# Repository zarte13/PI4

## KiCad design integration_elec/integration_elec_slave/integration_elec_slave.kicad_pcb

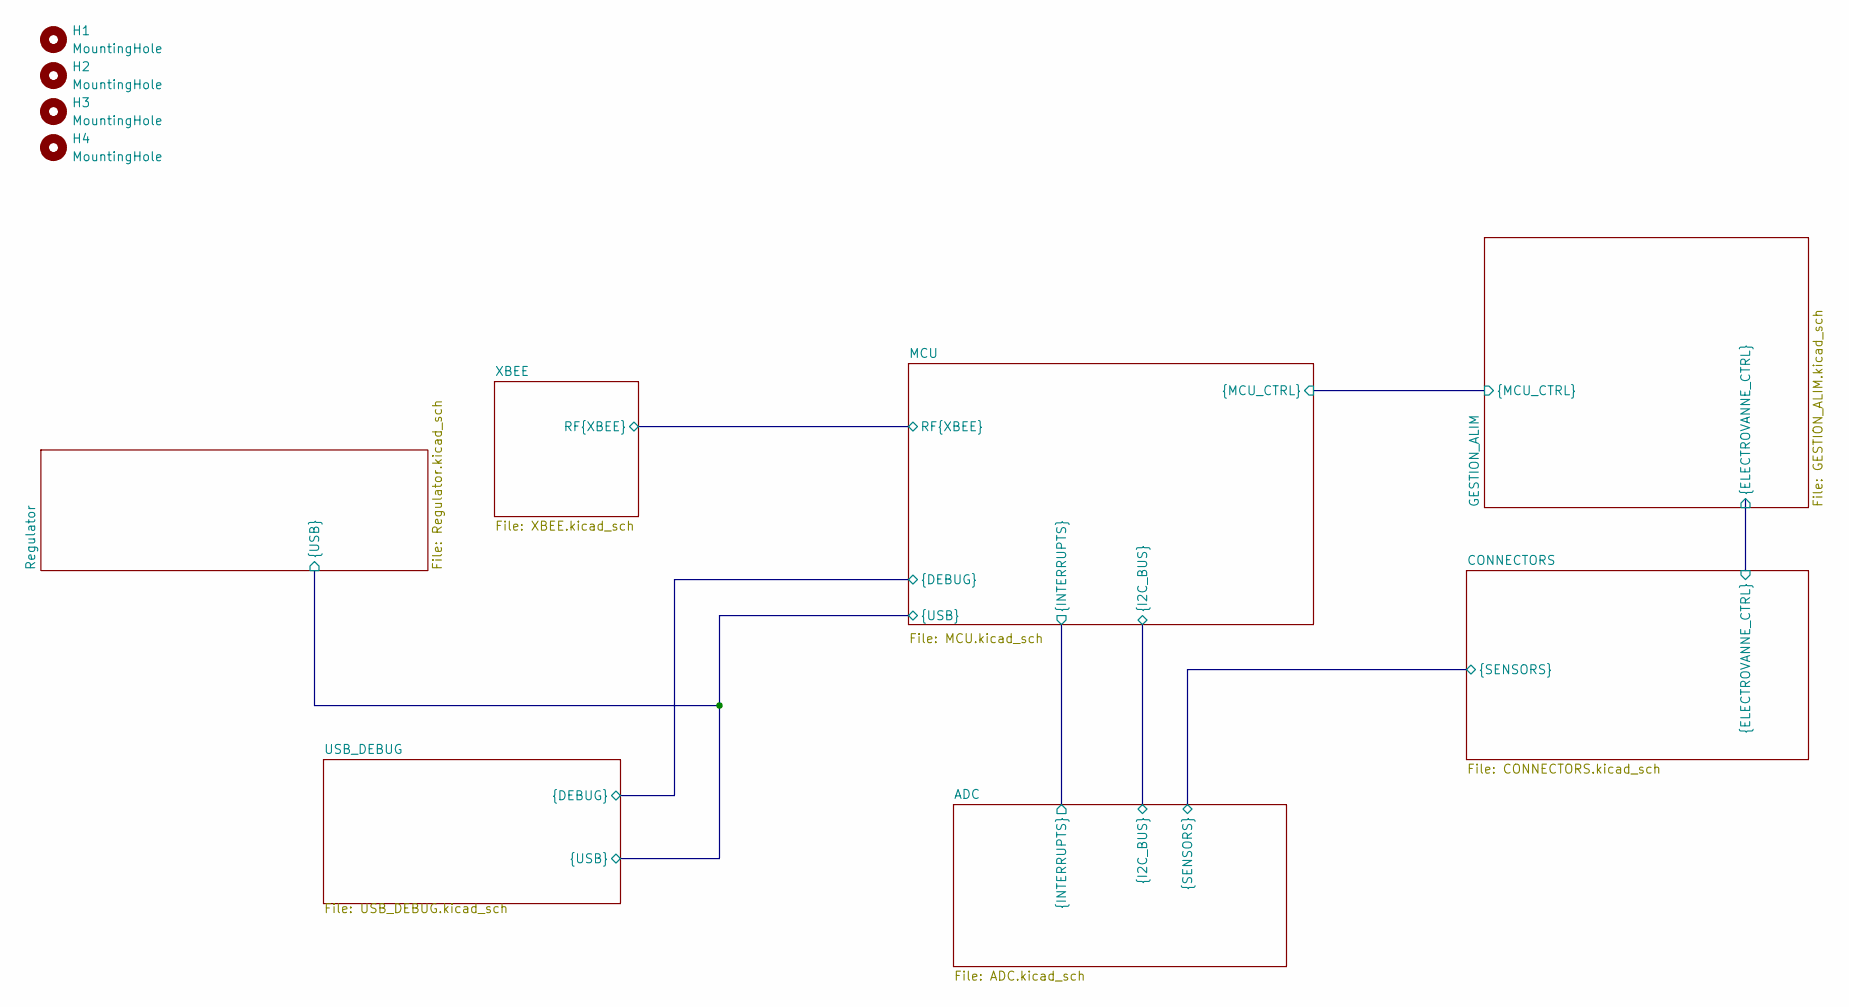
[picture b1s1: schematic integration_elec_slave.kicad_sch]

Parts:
H1, H2, H3, H4: MountingHole; MountingHole_3.2mm_M3

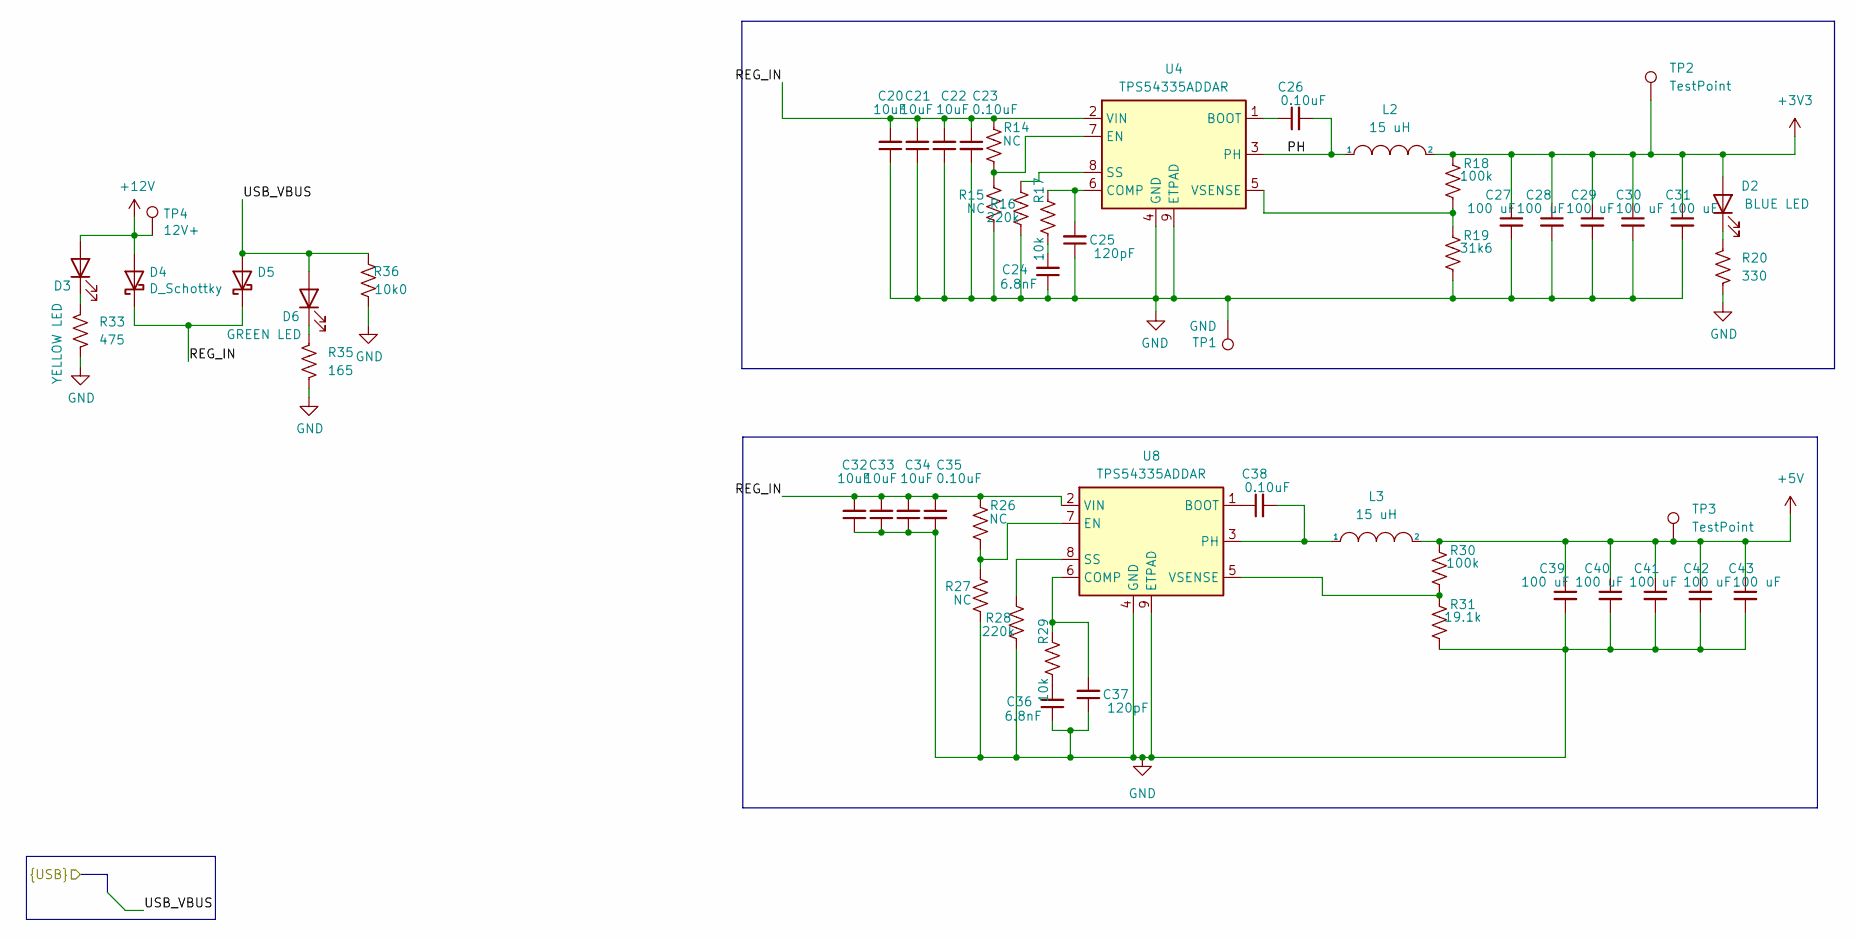
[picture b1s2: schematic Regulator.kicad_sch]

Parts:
C20, C21, C22, C32, C33, C34: 10uF; C_0805_2012Metric_Pad1.18x1.45mm_HandSolder; Manufacturer Part Number CL21A106KOQNNNE; DigiKey 1276-1096-1-ND
C23, C26, C35, C38: 0.10uF; C_0805_2012Metric_Pad1.18x1.45mm_HandSolder; Manufacturer Part Number CL21B104KBCNNNC; DigiKey 1276-1003-2-ND
C24, C36: 6.8nF; C_0805_2012Metric_Pad1.18x1.45mm_HandSolder; Manufacturer Part Number C0805C682K5RAC7800; DigiKey 399-C0805C682K5RAC7800TR-ND
C25, C37: 120pF; C_0805_2012Metric_Pad1.18x1.45mm_HandSolder; Manufacturer Part Number C0805C121J5GAC7800; DigiKey 399-C0805C121J5GAC7800TR-ND
C27, C28, C29, C30, C31, C39, C40, C41, C42, C43: 100 uF; C_1206_3216Metric; Manufacturer Part Number GRM31CR61A107MEA8L; DigiKey 490-GRM31CR61A107MEA8LTR-ND
D2: BLUE LED; LED_0805_2012Metric_Pad1.15x1.40mm_HandSolder; Manufacturer Part Number 5973605607F; DigiKey 350-4394-1-ND
D3: YELLOW LED; LED_1206_3216Metric; Manufacturer Part Number QTLP650D3TR; DigiKey 1080-1418-2-ND
D4, D5: D_Schottky; SOD323-HE; Manufacturer Part Number MBR1060HEWS_R1_00001; DigiKey 3757-MBR1060HEWS_R1_00001CT-ND
D6: GREEN LED; LED_1206_3216Metric; Manufacturer Part Number 5973605607F; DigiKey 350-4394-1-ND
L2, L3: 15 uH; IND_BOURNS_SRR1280; Manufacturer Part Number SRR1280-150M; DigiKey SRR1280-150MTR-ND
R14, R15, R26, R27: NC; R_0805_2012Metric_Pad1.20x1.40mm_HandSolder
R16, R28: 220k; R_0805_2012Metric_Pad1.20x1.40mm_HandSolder; Manufacturer Part Number CRG0805F220K; DigiKey A126350CT-ND
R17, R29: 10k; R_0805_2012Metric_Pad1.20x1.40mm_HandSolder; Manufacturer Part Number RC0805FR-0710KL; DigiKey 311-10.0KCRCT-ND
R18, R30: 100k; R_0805_2012Metric_Pad1.20x1.40mm_HandSolder; Manufacturer Part Number RC0805FR-07100KL; DigiKey 311-100KCRTR-ND
R19: 31k6; R_0805_2012Metric_Pad1.20x1.40mm_HandSolder; Manufacturer Part Number RC0805FR-0731K6L; DigiKey 311-31.6KCRTR-ND
R20: 330; R_0805_2012Metric_Pad1.20x1.40mm_HandSolder; Manufacturer Part Number RC0805JR-07330RL; DigiKey 311-330ARCT-ND
R31: 19.1k; R_0805_2012Metric_Pad1.20x1.40mm_HandSolder; DigiKey 311-19.1KCRCT-ND
R33: 475; R_0805_2012Metric_Pad1.20x1.40mm_HandSolder; Manufacturer Part Number RNCP0805FTD475R; DigiKey RNCP0805FTD475RTR-ND
R35: 165; R_0805_2012Metric_Pad1.20x1.40mm_HandSolder; Manufacturer Part Number RC0805FR-07165RL; DigiKey 311-165CRTR-ND
R36: 10k0; R_0603_1608Metric_Pad0.98x0.95mm_HandSolder; Manufacturer Part Number RC0805FR-0710KL; DigiKey 311-10.0KHRCT-ND
TP1: GND; TestPoint_Plated_Hole_D2.0mm
TP2, TP3: TestPoint; TestPoint_Plated_Hole_D2.0mm
TP4: 12V+; TestPoint_Plated_Hole_D2.0mm
U4, U8: TPS54335ADDAR; TI_SO-PowerPAD-8_ThermalVias; Manufacturer Part Number TPS54335ADDAR; DigiKey 296-TPS54335ADDARTR-ND

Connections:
+3V3: C27.1, C28.1, C29.1, C30.1, C31.1, D2.2 (A), L2.2, R18.1, TP2.1; also elsewhere on the board
+5V: C39.1, C40.1, C41.1, C42.1, C43.1, L3.2, R30.1, TP3.1; also elsewhere on the board
+12V: D3.2 (A), D4.2 (A), TP4.1; also elsewhere on the board
/MCU/USB_VBUS: D5.2 (A), D6.2 (A), R36.1; also elsewhere on the board
/Regulator/PH: C26.2, L2.1, U4.3 (PH)
/Regulator/REG_IN: C20.2, C21.2, C22.2, C23.1, C32.2, C33.2, C34.2, C35.1, D4.1 (K), D5.1 (K), R14.1, R26.1, U4.2 (VIN), U8.2 (VIN)
GND: C20.1, C21.1, C22.1, C23.2, C24.1, C25.1, C27.2, C28.2, C29.2, C30.2, C31.2, C32.1, C33.1, C34.1, C35.2, C36.1, C37.1, C39.2, C40.2, C41.2, C42.2, C43.2, R15.2, R16.2, R19.2, R20.2, R27.2, R28.2, R31.2, R33.2, R35.2, R36.2, TP1.1, U4.4 (GND), U4.9 (ETPAD), U8.4 (GND), U8.9 (ETPAD); also elsewhere on the board
unnamed: C24.2, R17.2
unnamed: C36.2, R29.2
unnamed: D2.1 (K), R20.1
unnamed: D3.1 (K), R33.1
unnamed: D6.1 (K), R35.1
unnamed: C26.1, U4.1 (BOOT)
unnamed: C25.2, R17.1, U4.6 (COMP)
unnamed: R14.2, R15.1, U4.7 (EN)
unnamed: R16.1, U4.8 (SS)
unnamed: R18.2, R19.1, U4.5 (VSENSE)
unnamed: C38.1, U8.1 (BOOT)
unnamed: C37.2, R29.1, U8.6 (COMP)
unnamed: R26.2, R27.1, U8.7 (EN)
unnamed: C38.2, L3.1, U8.3 (PH)
unnamed: R28.1, U8.8 (SS)
unnamed: R30.2, R31.1, U8.5 (VSENSE)

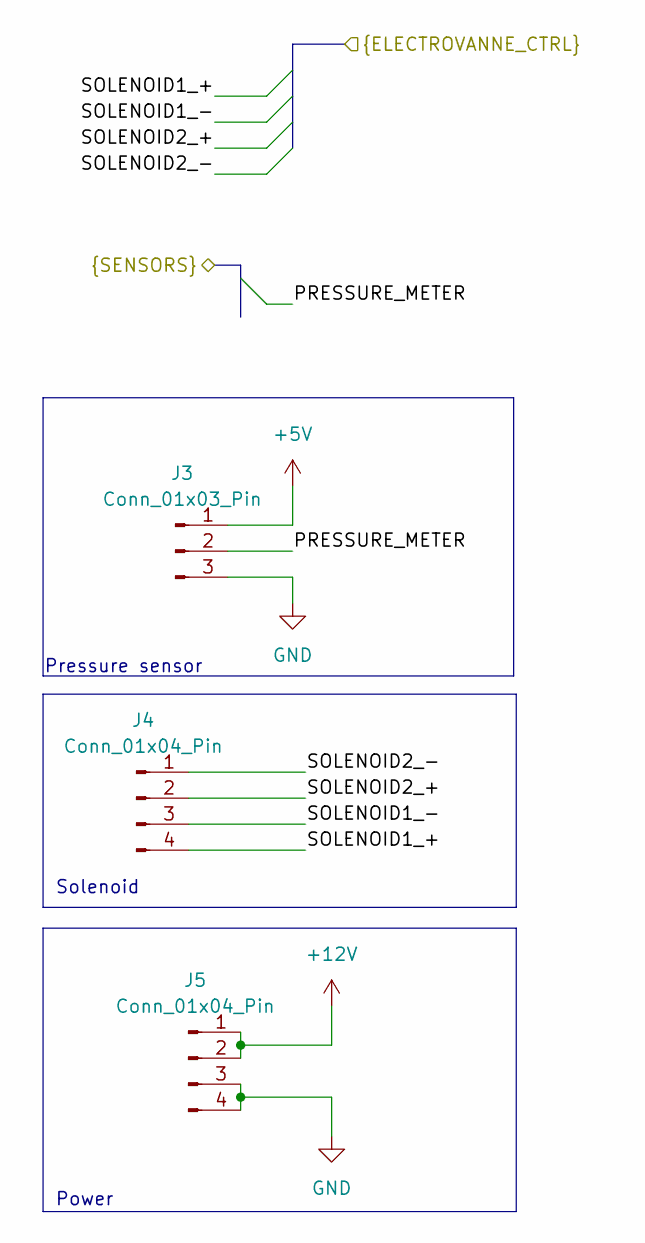
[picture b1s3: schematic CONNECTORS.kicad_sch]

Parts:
J3: Conn_01x03_Pin; Molex_Micro-Fit_3.0_43650-0315_1x03_P3.00mm_Vertical; DigiKey 538-43650-0315
J4, J5: Conn_01x04_Pin; Molex_Micro-Fit_3.0_43650-0415_1x04_P3.00mm_Vertical; DigiKey WM1919-ND

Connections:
+5V: J3.1; also elsewhere on the board
+12V: J5.1, J5.2; also elsewhere on the board
/ADC/PRESSURE_METER: J3.2; also elsewhere on the board
/CONNECTORS/SOLENOID1_+: J4.4; also elsewhere on the board
/CONNECTORS/SOLENOID1_-: J4.3; also elsewhere on the board
/CONNECTORS/SOLENOID2_+: J4.2; also elsewhere on the board
/CONNECTORS/SOLENOID2_-: J4.1; also elsewhere on the board
GND: J3.3, J5.3, J5.4; also elsewhere on the board

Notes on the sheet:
Pressure sensor
Power
Solenoid

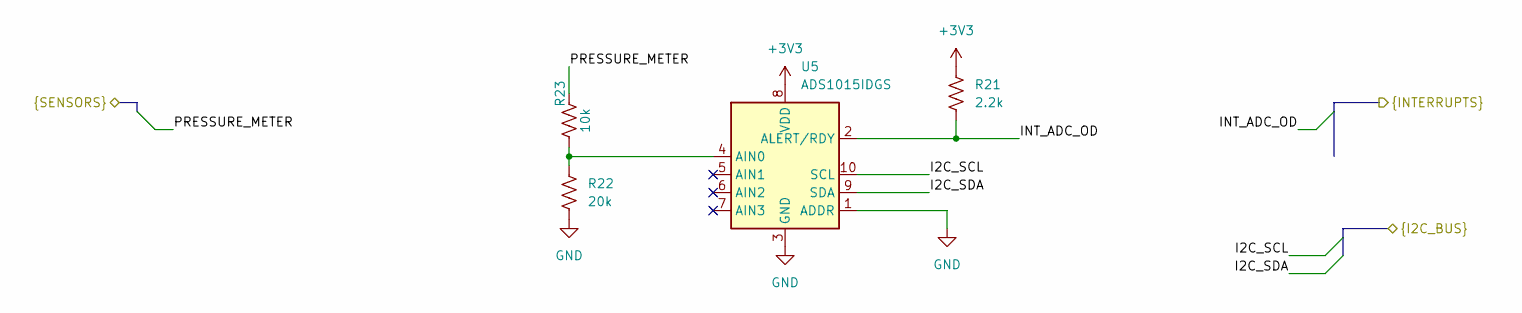
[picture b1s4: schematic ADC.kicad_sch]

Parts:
R21: 2.2k; R_0805_2012Metric_Pad1.20x1.40mm_HandSolder; DigiKey 311-2.20KCRCT-ND
R22: 20k; R_0805_2012Metric_Pad1.20x1.40mm_HandSolder; DigiKey P20KDACT-ND
R23: 10k; R_0805_2012Metric_Pad1.20x1.40mm_HandSolder; Manufacturer Part Number RC0805FR-0710KL; DigiKey 311-10.0KCRCT-ND
U5: ADS1015IDGS; TSSOP-10_3x3mm_P0.5mm; DigiKey 595-ADS1015IDGSR

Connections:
+3V3: R21.1, U5.8 (VDD); also elsewhere on the board
/ADC/I2C_SCL: U5.10 (SCL); also elsewhere on the board
/ADC/I2C_SDA: U5.9 (SDA); also elsewhere on the board
/ADC/INT_ADC_OD: R21.2, U5.2 (ALERT/RDY); also elsewhere on the board
/ADC/PRESSURE_METER: R23.1; also elsewhere on the board
GND: R22.2, U5.1 (ADDR), U5.3 (GND); also elsewhere on the board
unnamed: R22.1, R23.2, U5.4 (AIN0)

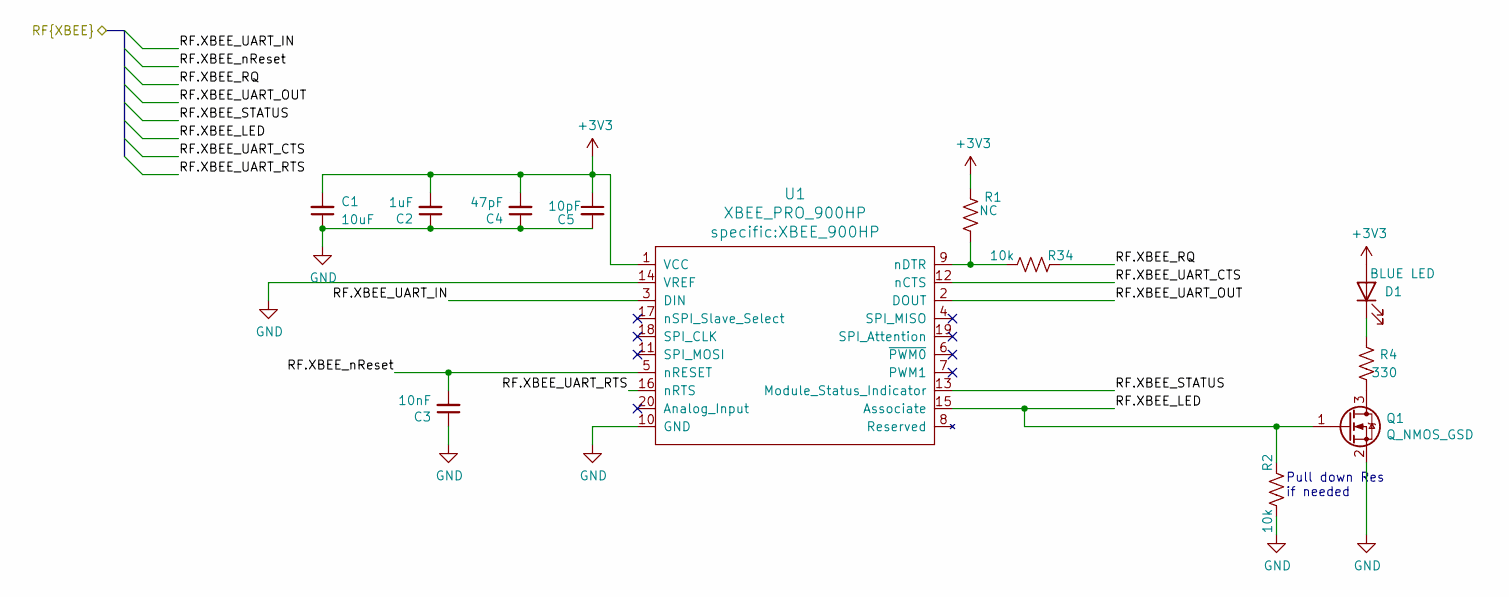
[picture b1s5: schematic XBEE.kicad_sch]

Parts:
C1: 10uF; C_0805_2012Metric_Pad1.18x1.45mm_HandSolder; Manufacturer Part Number CL21A106KOQNNNE; DigiKey 1276-1096-1-ND
C2: 1uF; C_0805_2012Metric_Pad1.18x1.45mm_HandSolder; Manufacturer Part Number C0805C105K4RAC7800; DigiKey 399-C0805C105K4RAC7800TR-ND
C3: 10nF; C_0805_2012Metric_Pad1.18x1.45mm_HandSolder; Manufacturer Part Number CL21B103KBANNNC; DigiKey 1276-1015-1-ND
C4: 47pF; C_0805_2012Metric_Pad1.18x1.45mm_HandSolder; Manufacturer Part Number C0805C470J5GAC7210; DigiKey 399-C0805C470J5GAC7210TR-ND
C5: 10pF; C_0805_2012Metric_Pad1.18x1.45mm_HandSolder; Manufacturer Part Number C0805C100J5GAC7800; DigiKey 399-C0805C100J5GAC7800TR-ND
D1: BLUE LED; LED_0805_2012Metric_Pad1.15x1.40mm_HandSolder; Manufacturer Part Number 5973605607F; DigiKey 350-4394-1-ND
Q1: Q_NMOS_GSD; SOT-23; Manufacturer Part Number 2N7002-TP; DigiKey 2N7002-TPMSCT-ND
R1: NC; R_0805_2012Metric_Pad1.20x1.40mm_HandSolder
R2, R34: 10k; R_0805_2012Metric_Pad1.20x1.40mm_HandSolder; Manufacturer Part Number RC0805FR-0710KL; DigiKey 311-10.0KCRCT-ND
R4: 330; R_0805_2012Metric_Pad1.20x1.40mm_HandSolder; Manufacturer Part Number RC0805JR-07330RL; DigiKey 311-330ARCT-ND
U1: XBEE_PRO_900HP; XBEE_900HP; Manufacturer Part Number XBP9B-DMST-002; DigiKey 602-1299-ND

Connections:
+3V3: C1.2, C2.2, C4.2, C5.1, D1.2 (A), R1.1, U1.1 (VCC); also elsewhere on the board
/MCU/RF.XBEE_LED: Q1.1 (G), R2.1, U1.15 (Associate); also elsewhere on the board
/MCU/RF.XBEE_RQ: R34.1; also elsewhere on the board
/MCU/RF.XBEE_STATUS: U1.13 (Module_Status_Indicator); also elsewhere on the board
/MCU/RF.XBEE_UART_CTS: U1.12 (nCTS); also elsewhere on the board
/MCU/RF.XBEE_UART_IN: U1.3 (DIN); also elsewhere on the board
/MCU/RF.XBEE_UART_OUT: U1.2 (DOUT); also elsewhere on the board
/MCU/RF.XBEE_UART_RTS: U1.16 (nRTS); also elsewhere on the board
/MCU/RF.XBEE_nReset: C3.2, U1.5 (nRESET); also elsewhere on the board
GND: C1.1, C2.1, C3.1, C4.1, C5.2, Q1.2 (S), R2.2, U1.10 (GND), U1.14 (VREF); also elsewhere on the board
unnamed: D1.1 (K), R4.1
unnamed: Q1.3 (D), R4.2
unnamed: R1.2, R34.2, U1.9 (nDTR)

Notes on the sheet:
Pull down Res if needed

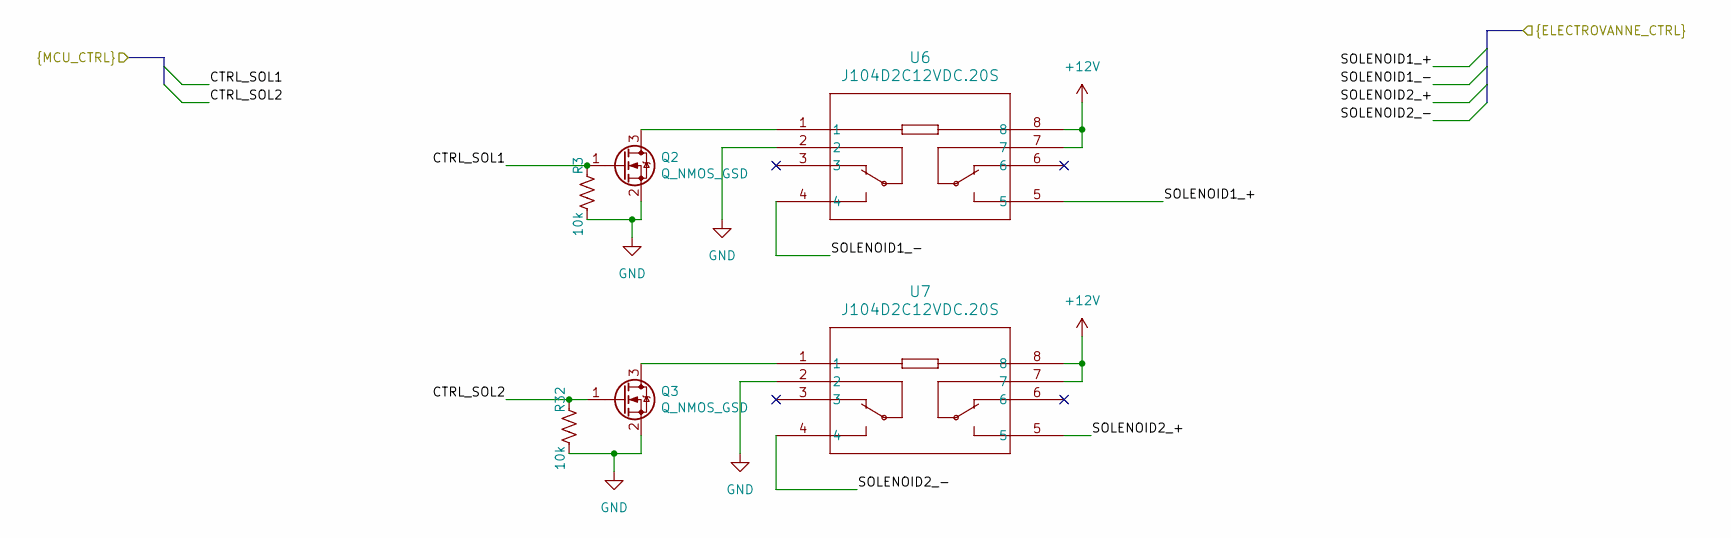
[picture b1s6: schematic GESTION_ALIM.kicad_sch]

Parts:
Q2, Q3: Q_NMOS_GSD; SOT-23; Manufacturer Part Number SQ2308CES-T1_GE3; DigiKey SQ2308CES-T1_GE3CT-ND
R3, R32: 10k; R_0805_2012Metric_Pad1.20x1.40mm_HandSolder; Manufacturer Part Number RC0805FR-0710KL; DigiKey 311-10.0KCRCT-ND
U6, U7: J104D2C12VDC.20S; RELAY8_J104D2C12VDC.20S_CRS; DigiKey 2449-J104D2C12VDC.20S-ND

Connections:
+12V: U6.7, U6.8, U7.7, U7.8; also elsewhere on the board
/CONNECTORS/SOLENOID1_+: U6.5; also elsewhere on the board
/CONNECTORS/SOLENOID1_-: U6.4; also elsewhere on the board
/CONNECTORS/SOLENOID2_+: U7.5; also elsewhere on the board
/CONNECTORS/SOLENOID2_-: U7.4; also elsewhere on the board
/GESTION_ALIM/CTRL_SOL1: Q2.1 (G), R3.1; also elsewhere on the board
/GESTION_ALIM/CTRL_SOL2: Q3.1 (G), R32.1; also elsewhere on the board
GND: Q2.2 (S), Q3.2 (S), R3.2, R32.2, U6.2, U7.2; also elsewhere on the board
unnamed: Q2.3 (D), U6.1
unnamed: Q3.3 (D), U7.1

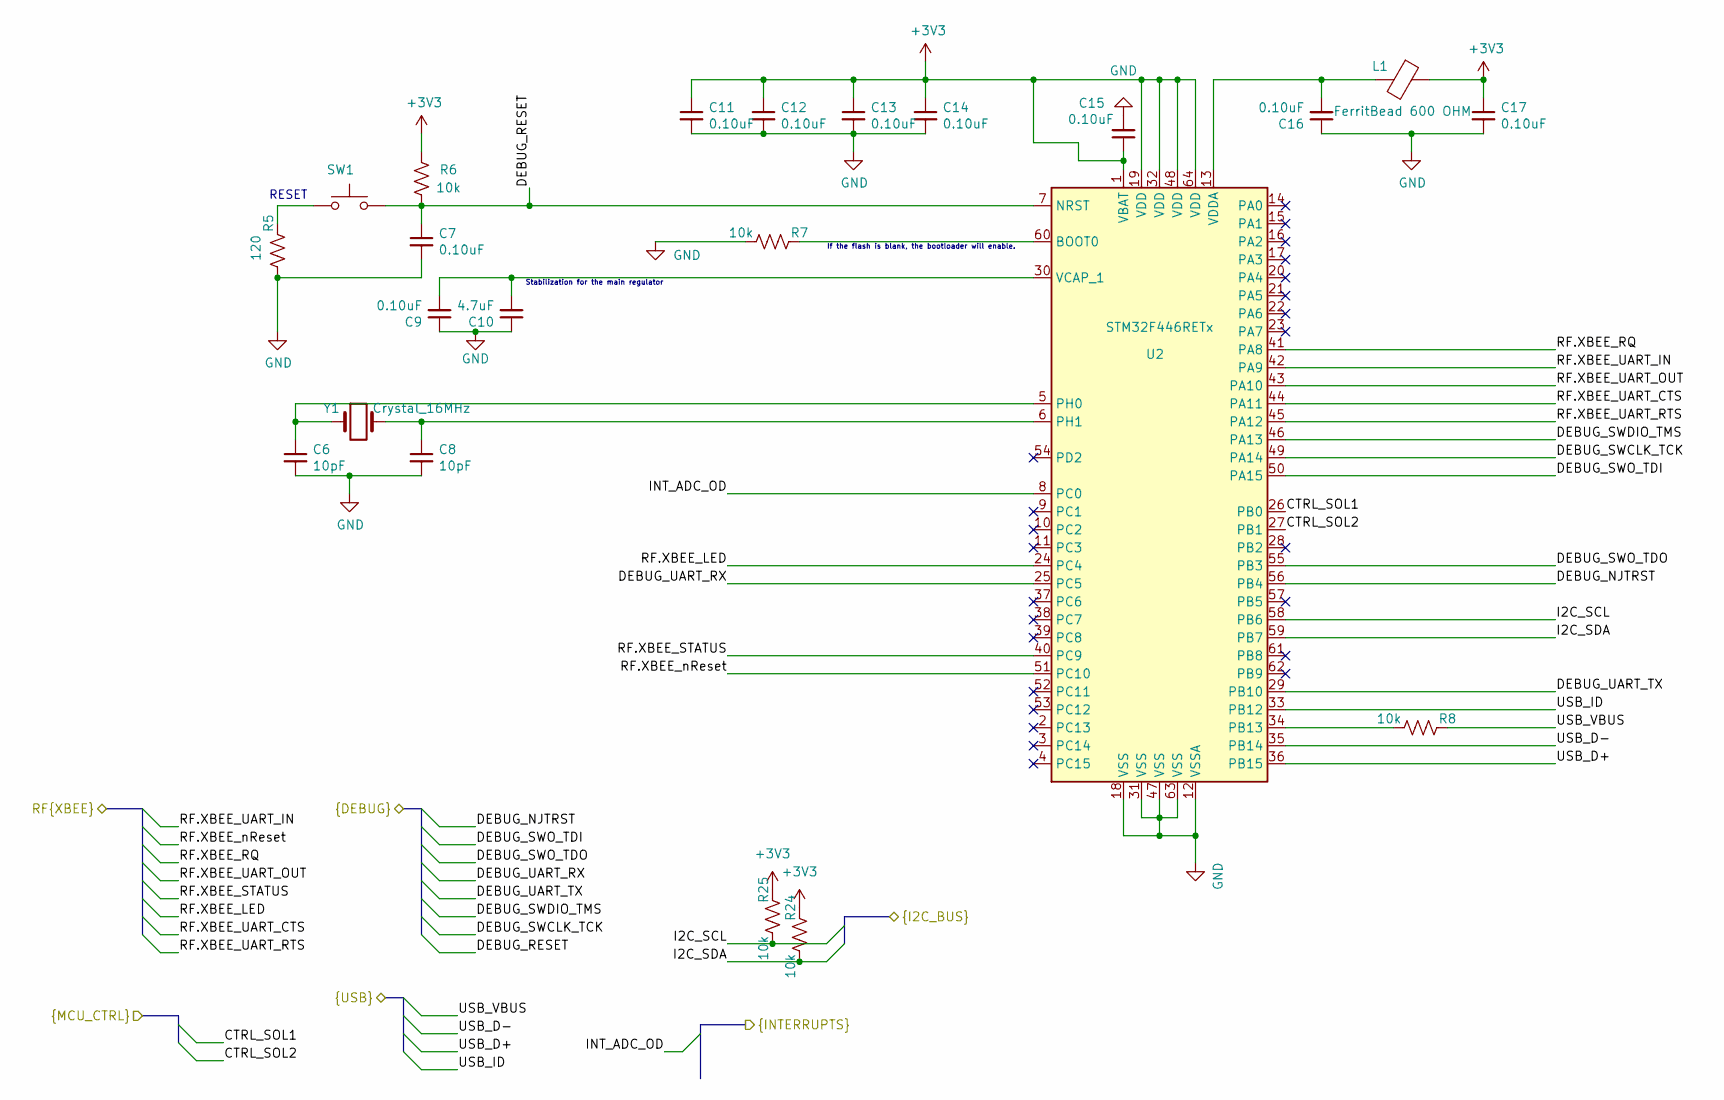
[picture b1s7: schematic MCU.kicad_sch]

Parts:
C6, C8: 10pF; C_0805_2012Metric_Pad1.18x1.45mm_HandSolder; Manufacturer Part Number C0805C100J5GAC7800; DigiKey 399-C0805C100J5GAC7800TR-ND
C7, C9, C11, C12, C13, C14, C15, C16, C17: 0.10uF; C_0805_2012Metric_Pad1.18x1.45mm_HandSolder; Manufacturer Part Number CL21B104KBCNNNC; DigiKey 1276-1003-2-ND
C10: 4.7uF; C_0805_2012Metric_Pad1.18x1.45mm_HandSolder; Manufacturer Part Number CL21A475KOFNNNE; DigiKey 1276-1065-1-ND
L1: FerritBead 600 OHM; L_0805_2012Metric_Pad1.15x1.40mm_HandSolder; Manufacturer Part Number 742792040; DigiKey 732-1620-1-ND
R5: 120; R_0805_2012Metric_Pad1.20x1.40mm_HandSolder; Manufacturer Part Number RC0805JR-07120RL; DigiKey 311-120ARCT-ND
R6, R7, R8, R24, R25: 10k; R_0805_2012Metric_Pad1.20x1.40mm_HandSolder; Manufacturer Part Number RC0805FR-0710KL; DigiKey 311-10.0KCRCT-ND
SW1: SW_Push; SW_SPST_TL3342; Manufacturer Part Number TL3342F160QG/TR; DigiKey EG2531CT-ND
U2: STM32F446RETx; LQFP-64_10x10mm_P0.5mm; Manufacturer Part Number STM32F446RET6; DigiKey 497-15376-ND
Y1: Crystal_16MHz; CSM-3X; Manufacturer Part Number ECS-160-20-3X-TR; DigiKey XC1776CT-ND

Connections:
+3V3: C11.1, C12.1, C13.1, C14.1, C15.1, C17.1, L1.1, R6.1, R24.1, R25.1, U2.1 (VBAT), U2.19 (VDD), U2.32 (VDD), U2.48 (VDD), U2.64 (VDD); also elsewhere on the board
/ADC/I2C_SCL: R25.2, U2.58 (PB6); also elsewhere on the board
/ADC/I2C_SDA: R24.2, U2.59 (PB7); also elsewhere on the board
/ADC/INT_ADC_OD: U2.8 (PC0); also elsewhere on the board
/GESTION_ALIM/CTRL_SOL1: U2.26 (PB0); also elsewhere on the board
/GESTION_ALIM/CTRL_SOL2: U2.27 (PB1); also elsewhere on the board
/MCU/DEBUG_NJTRST: U2.56 (PB4); also elsewhere on the board
/MCU/DEBUG_RESET: C7.1, R6.2, SW1.2, U2.7 (NRST); also elsewhere on the board
/MCU/DEBUG_SWCLK_TCK: U2.49 (PA14); also elsewhere on the board
/MCU/DEBUG_SWDIO_TMS: U2.46 (PA13); also elsewhere on the board
/MCU/DEBUG_SWO_TDI: U2.50 (PA15); also elsewhere on the board
/MCU/DEBUG_SWO_TDO: U2.55 (PB3); also elsewhere on the board
/MCU/DEBUG_UART_RX: U2.25 (PC5); also elsewhere on the board
/MCU/DEBUG_UART_TX: U2.29 (PB10); also elsewhere on the board
/MCU/RF.XBEE_LED: U2.24 (PC4); also elsewhere on the board
/MCU/RF.XBEE_RQ: U2.41 (PA8); also elsewhere on the board
/MCU/RF.XBEE_STATUS: U2.40 (PC9); also elsewhere on the board
/MCU/RF.XBEE_UART_CTS: U2.44 (PA11); also elsewhere on the board
/MCU/RF.XBEE_UART_IN: U2.42 (PA9); also elsewhere on the board
/MCU/RF.XBEE_UART_OUT: U2.43 (PA10); also elsewhere on the board
/MCU/RF.XBEE_UART_RTS: U2.45 (PA12); also elsewhere on the board
/MCU/RF.XBEE_nReset: U2.51 (PC10); also elsewhere on the board
/MCU/USB_D+: U2.36 (PB15); also elsewhere on the board
/MCU/USB_D-: U2.35 (PB14); also elsewhere on the board
/MCU/USB_ID: U2.33 (PB12)
/MCU/USB_VBUS: R8.1; also elsewhere on the board
GND: C6.2, C7.2, C8.2, C9.1, C10.1, C11.2, C12.2, C13.2, C14.2, C15.2, C16.1, C17.2, R5.2, R7.2, U2.12 (VSSA), U2.18 (VSS), U2.31 (VSS), U2.47 (VSS), U2.63 (VSS); also elsewhere on the board
unnamed: R5.1, SW1.1
unnamed: R7.1, U2.60 (BOOT0)
unnamed: R8.2, U2.34 (PB13)
unnamed: C6.1, U2.5 (PH0), Y1.1
unnamed: C8.1, U2.6 (PH1), Y1.2
unnamed: C9.2, C10.2, U2.30 (VCAP_1)
unnamed: C16.2, L1.2, U2.13 (VDDA)

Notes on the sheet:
RESET
If the flash is blank, the bootloader will enable.
Stabilization for the main regulator

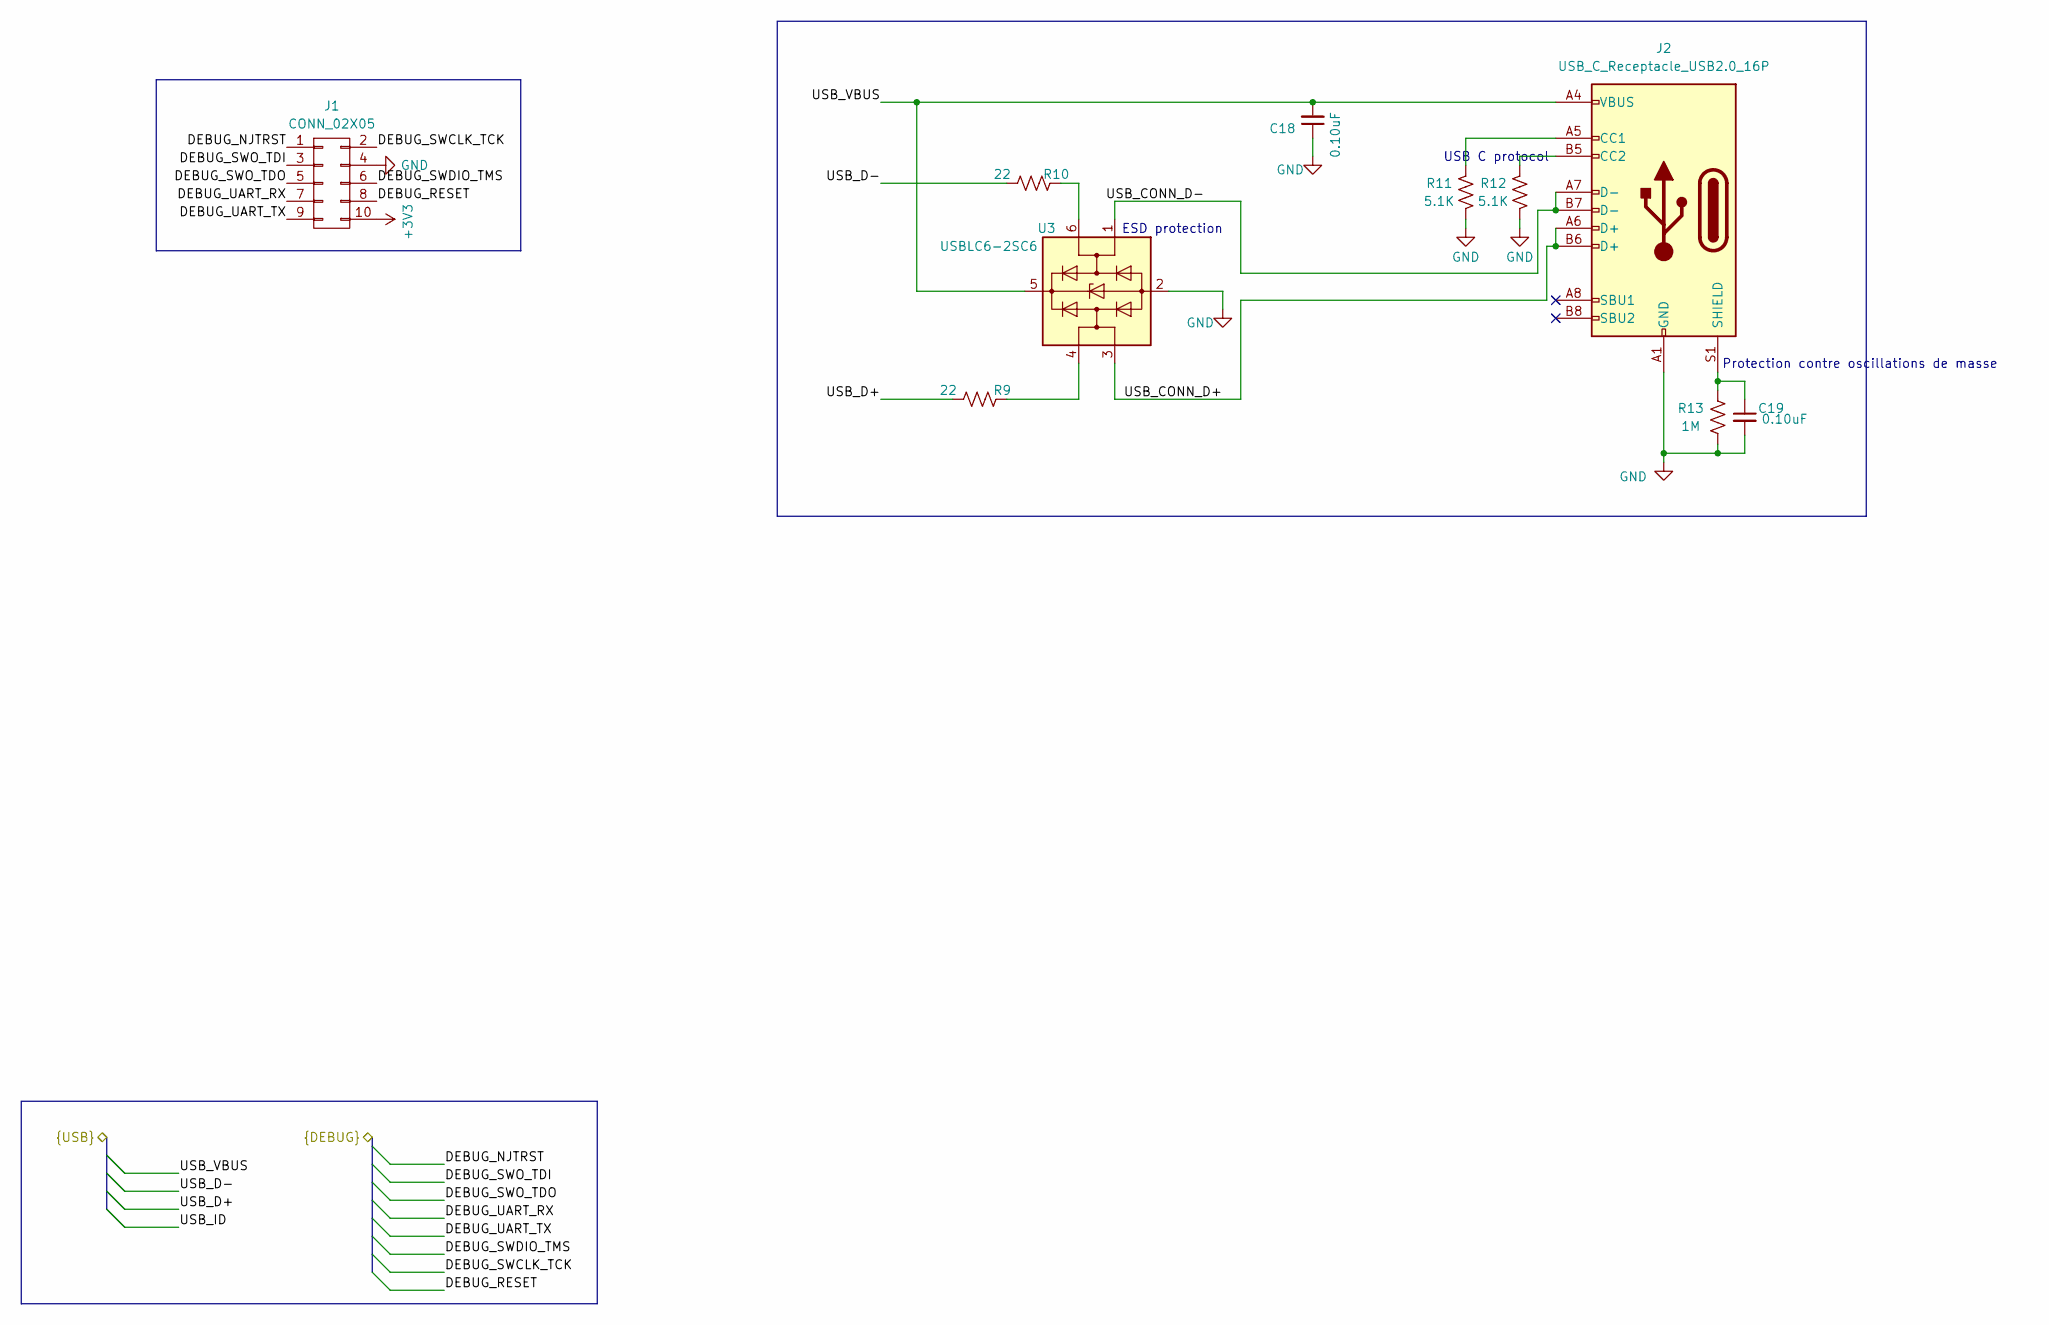
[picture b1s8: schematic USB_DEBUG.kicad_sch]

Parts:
C18, C19: 0.10uF; C_0805_2012Metric_Pad1.18x1.45mm_HandSolder; Manufacturer Part Number CL21B104KBCNNNC; DigiKey 1276-1003-2-ND
J1: CONN_02X05; CONN_CNC_10_pins; DigiKey 1175-1627-ND
J2: USB_C_Receptacle_USB2.0_16P; USB_C_Receptacle_GCT_USB4105-xx-A_16P_TopMnt_Horizontal; DigiKey 2073-USB4105-GF-ACT-ND
R9, R10: 22; R_0805_2012Metric_Pad1.20x1.40mm_HandSolder; Manufacturer Part Number RC0805JR-0722RL; DigiKey 311-22ARCT-ND
R11, R12: 5.1K; R_0603_1608Metric_Pad0.98x0.95mm_HandSolder; DigiKey 311-5.10KHRCT-ND
R13: 1M; R_0805_2012Metric_Pad1.20x1.40mm_HandSolder; Manufacturer Part Number RC0805FR-071ML; DigiKey 311-1.00MCRTR-ND
U3: USBLC6-2SC6; SOT-23-6; Manufacturer Part Number USBLC6-2SC6Y; DigiKey 497-11882-1-ND

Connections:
+3V3: J1.10; also elsewhere on the board
/MCU/DEBUG_NJTRST: J1.1; also elsewhere on the board
/MCU/DEBUG_RESET: J1.8; also elsewhere on the board
/MCU/DEBUG_SWCLK_TCK: J1.2; also elsewhere on the board
/MCU/DEBUG_SWDIO_TMS: J1.6; also elsewhere on the board
/MCU/DEBUG_SWO_TDI: J1.3; also elsewhere on the board
/MCU/DEBUG_SWO_TDO: J1.5; also elsewhere on the board
/MCU/DEBUG_UART_RX: J1.7; also elsewhere on the board
/MCU/DEBUG_UART_TX: J1.9; also elsewhere on the board
/MCU/USB_D+: R9.2; also elsewhere on the board
/MCU/USB_D-: R10.2; also elsewhere on the board
/MCU/USB_VBUS: C18.2, J2.A4 (VBUS), J2.A9 (VBUS), J2.B4 (VBUS), J2.B9 (VBUS), U3.5 (VBUS); also elsewhere on the board
/USB_DEBUG/USB_CONN_D+: J2.A6 (D+), J2.B6 (D+), U3.3 (I/O2)
/USB_DEBUG/USB_CONN_D-: J2.A7 (D-), J2.B7 (D-), U3.1 (I/O1)
GND: C18.1, C19.2, J1.4, J2.A1 (GND), J2.A12 (GND), J2.B1 (GND), J2.B12 (GND), R11.2, R12.2, R13.1, U3.2 (GND); also elsewhere on the board
unnamed: J2.A5 (CC1), R11.1
unnamed: J2.B5 (CC2), R12.1
unnamed: C19.1, J2.S1 (SHIELD), R13.2
unnamed: R9.1, U3.4 (I/O2)
unnamed: R10.1, U3.6 (I/O1)

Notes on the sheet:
USB C protocol
ESD protection
Protection contre oscillations de masse
